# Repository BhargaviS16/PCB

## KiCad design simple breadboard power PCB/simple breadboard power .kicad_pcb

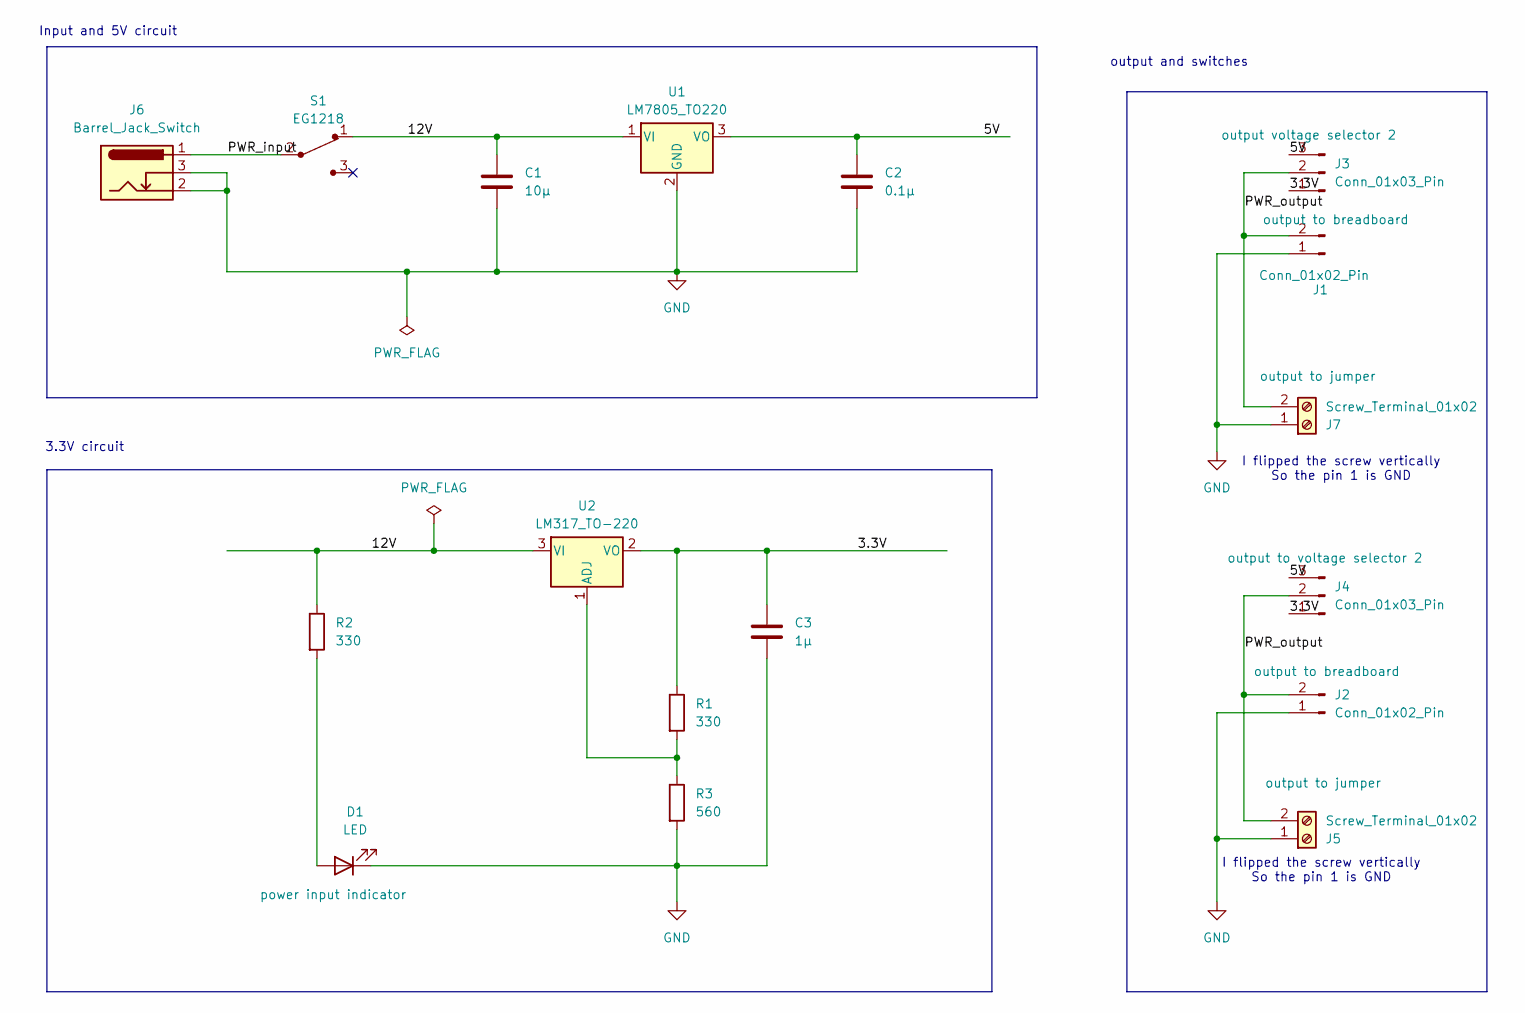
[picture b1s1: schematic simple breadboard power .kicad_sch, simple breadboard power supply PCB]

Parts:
C1: 10µ; C_Disc_D3.0mm_W1.6mm_P2.50mm
C2: 0.1µ; C_Disc_D3.0mm_W1.6mm_P2.50mm
C3: 1µ; C_Disc_D3.0mm_W1.6mm_P2.50mm
D1: LED; LED_D5.0mm
J1, J2: Conn_01x02_Pin; PinHeader_1x02_P2.54mm_Vertical
J3, J4: Conn_01x03_Pin; PinHeader_1x03_P2.54mm_Vertical
J5, J7: Screw_Terminal_01x02; TerminalBlock_bornier-2_P5.08mm
J6: Barrel_Jack_Switch; BarrelJack_Horizontal
R1, R2: 330; R_Axial_DIN0204_L3.6mm_D1.6mm_P7.62mm_Horizontal
R3: 560; R_Axial_DIN0204_L3.6mm_D1.6mm_P7.62mm_Horizontal
S1: EG1218; Switch_Slide_11.6x4mm_EG1218; MPN EG1218; Digi-Key_PN EG1903-ND
U1: LM7805_TO220; TO-220-3_Vertical
U2: LM317_TO-220; TO-220-3_Vertical

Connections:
/3.3V: C3.1, J3.1, J4.1, R1.1, U2.2 (VO)
/5V: C2.1, J3.3, J4.3, U1.3 (VO)
/12V: C1.1, R2.1, S1.1, U1.1 (VI), U2.3 (VI)
/PWR_input: J6.1, S1.2
/PWR_output: J1.2, J2.2, J3.2, J4.2, J5.2, J7.2
GND: C1.2, C2.2, C3.2, D1.1 (K), J1.1, J2.1, J5.1, J6.2, J6.3, J7.1, R3.2, U1.2 (GND)
unnamed: D1.2 (A), R2.2
unnamed: R1.2, R3.1, U2.1 (ADJ)

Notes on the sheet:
I flipped the screw vertically So the pin 1 is GND
Input and 5V circuit
output and switches
3.3V circuit

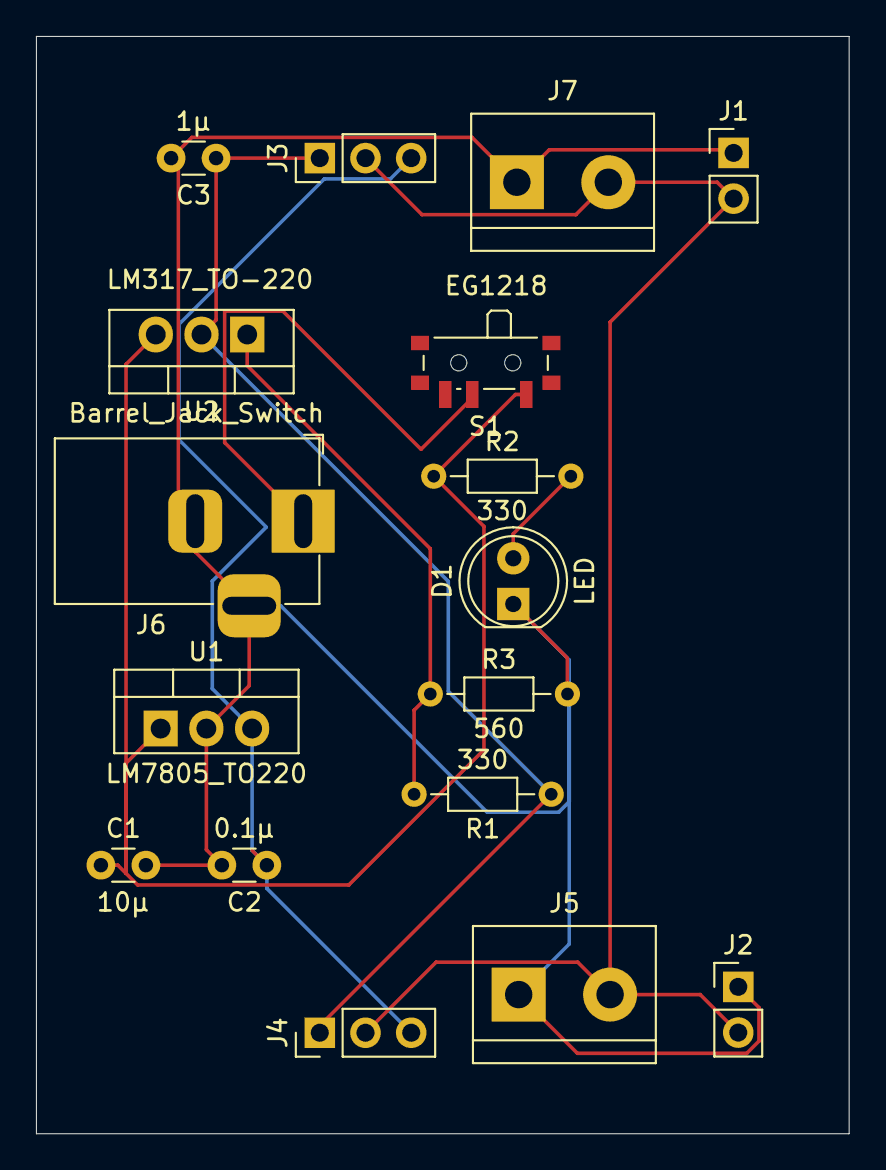
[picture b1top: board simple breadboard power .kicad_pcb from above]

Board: 2 copper layers, 45.1 x 61.0 mm, 17 parts (0 on the bottom side), 8 nets.

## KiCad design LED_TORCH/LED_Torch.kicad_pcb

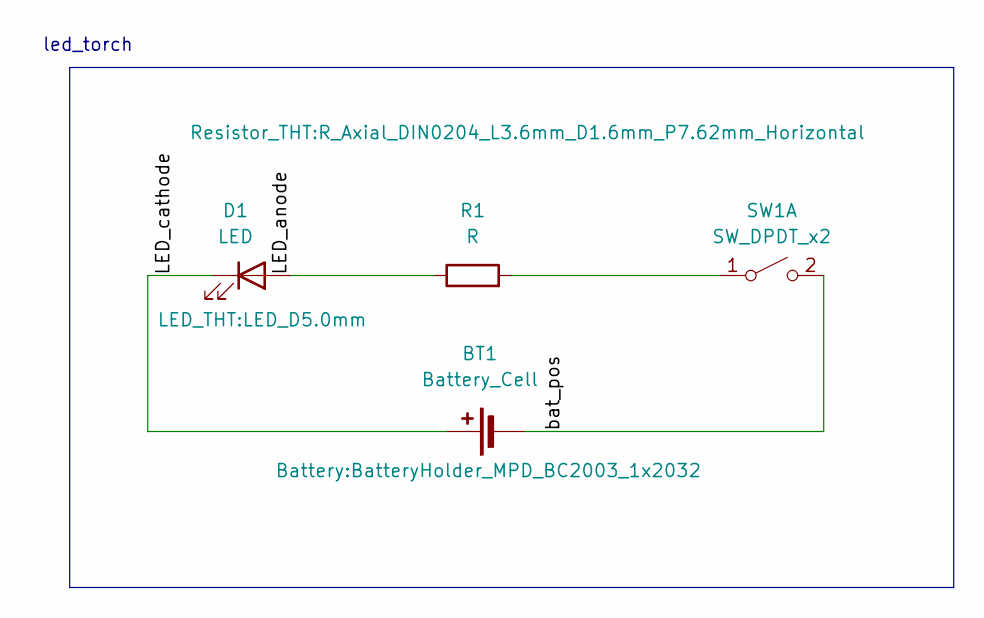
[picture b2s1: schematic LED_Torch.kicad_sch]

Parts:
BT1: Battery_Cell; BatteryHolder_MPD_BC2003_1x2032
D1: LED; LED_D5.0mm
R1: R; R_Axial_DIN0204_L3.6mm_D1.6mm_P7.62mm_Horizontal
SW1: SW_DPDT_x2; SW_TH_Tactile_Omron_B3F-10xx

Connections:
/LED_anode: D1.2 (A), R1.1
/LED_cathode: BT1.1 (+), D1.1 (K)
/bat_pos: BT1.2 (-), SW1.2 (B)
unnamed: R1.2, SW1.1 (A)

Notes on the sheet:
led_torch

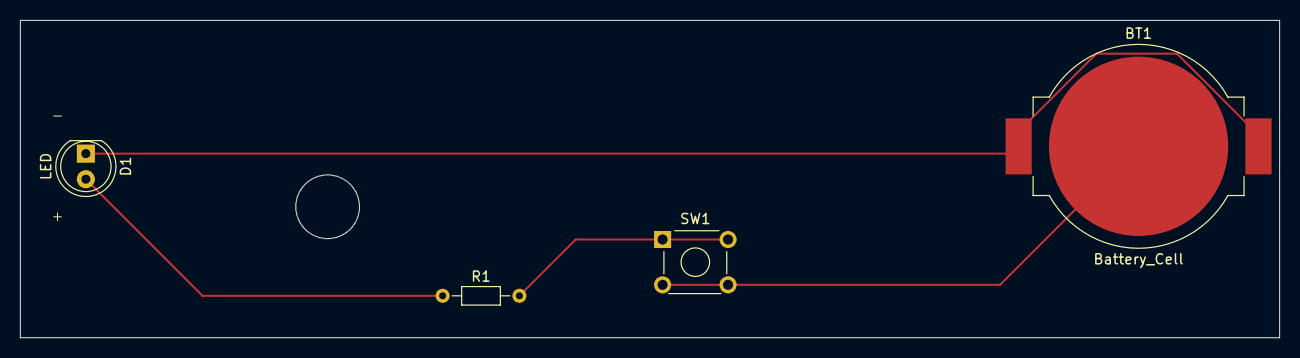
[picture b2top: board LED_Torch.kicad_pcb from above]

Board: 2 copper layers, 125.0 x 31.5 mm, 4 parts (0 on the bottom side), 4 nets.

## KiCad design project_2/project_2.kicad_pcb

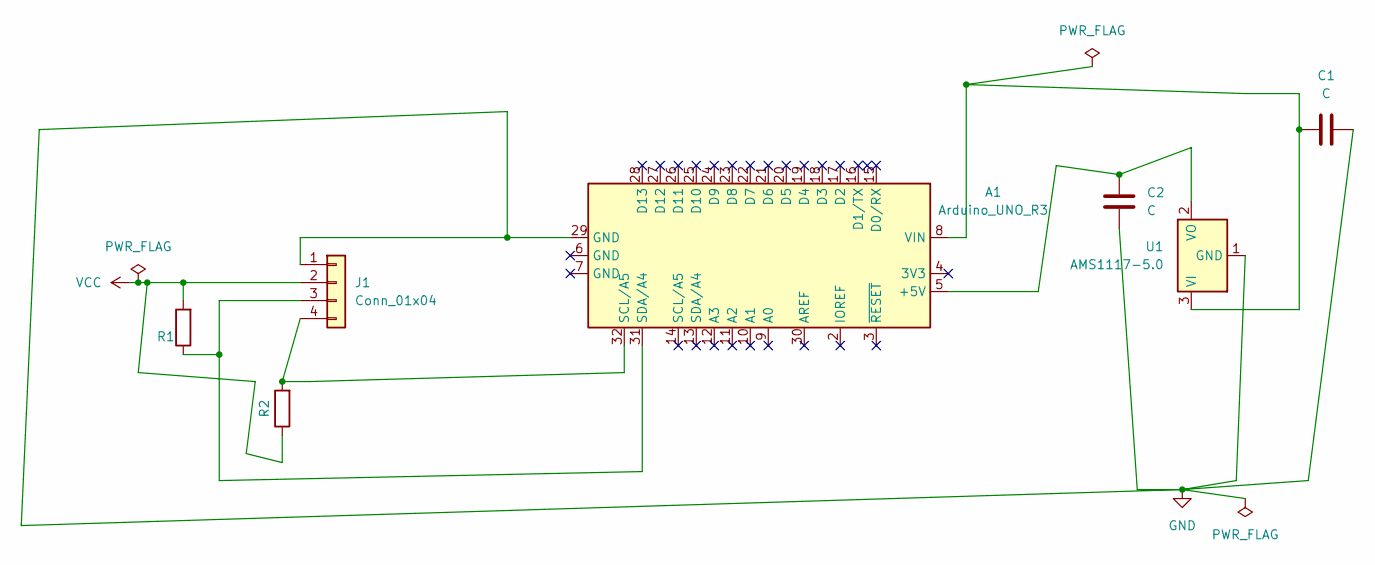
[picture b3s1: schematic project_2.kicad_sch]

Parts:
A1: Arduino_UNO_R3
C1, C2: C; C_Disc_D5.0mm_W2.5mm_P2.50mm
J1: Conn_01x04; PinHeader_1x04_P2.54mm_Vertical
R1, R2: 4.7k; R_Axial_DIN0207_L6.3mm_D2.5mm_P7.62mm_Horizontal
U1: AMS1117-5.0; SOT-223-3_TabPin2

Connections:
GND: A1.29 (GND), C1.2, C2.1, J1.1, U1.1 (GND)
unnamed: A1.5 (+5V), C2.2, U1.2 (VO)
unnamed: A1.8 (VIN), C1.1, U1.3 (VI)
unnamed: A1.31 (SDA/A4), J1.3, R1.1
unnamed: A1.32 (SCL/A5), J1.4, R2.2
VCC: J1.2, R1.2, R2.1

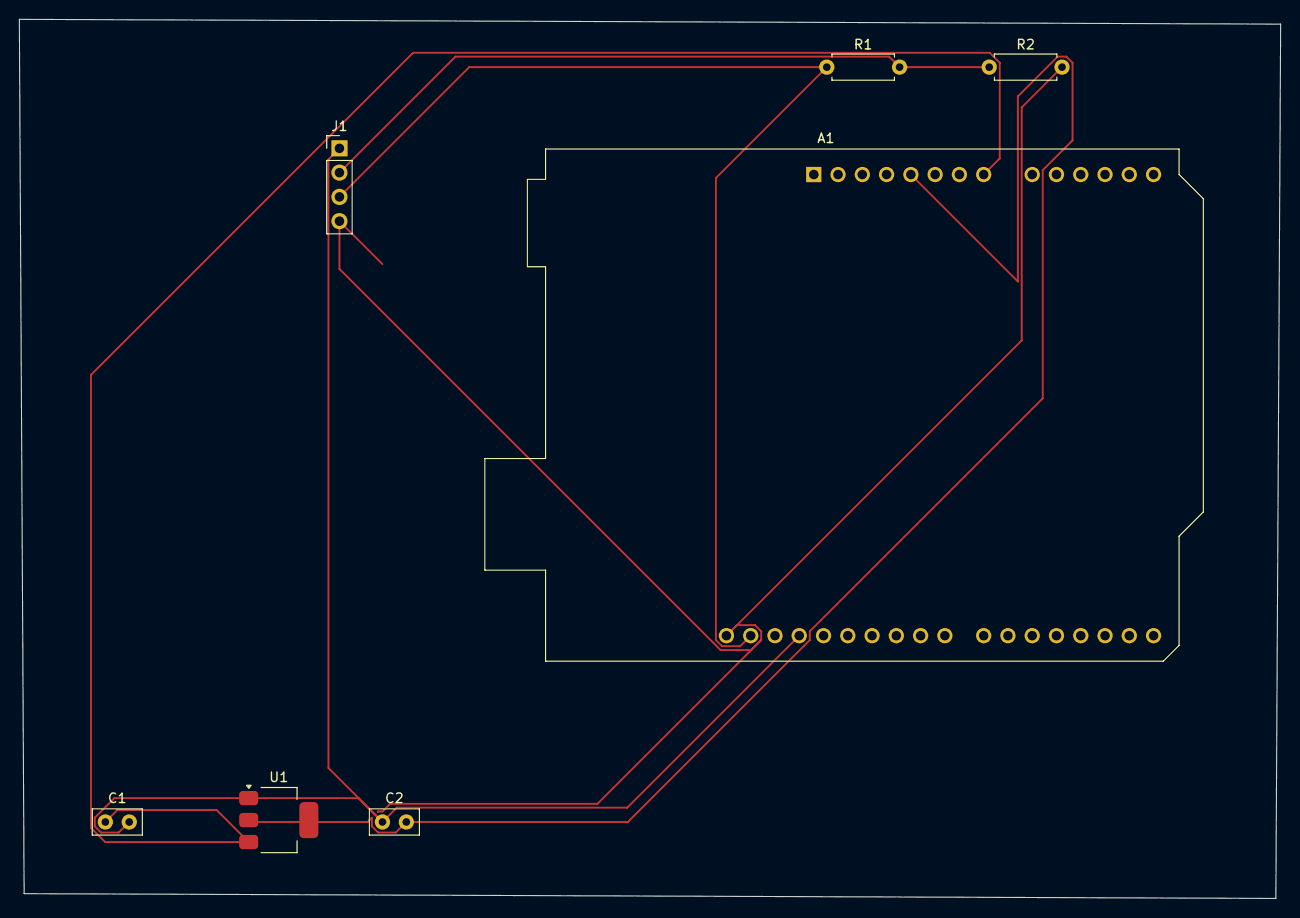
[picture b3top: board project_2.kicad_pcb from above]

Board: 2 copper layers, 132.0 x 92.0 mm, 7 parts (0 on the bottom side), 6 nets.
